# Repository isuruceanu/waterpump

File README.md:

# waterpump
water pump controller with digital pressure reader

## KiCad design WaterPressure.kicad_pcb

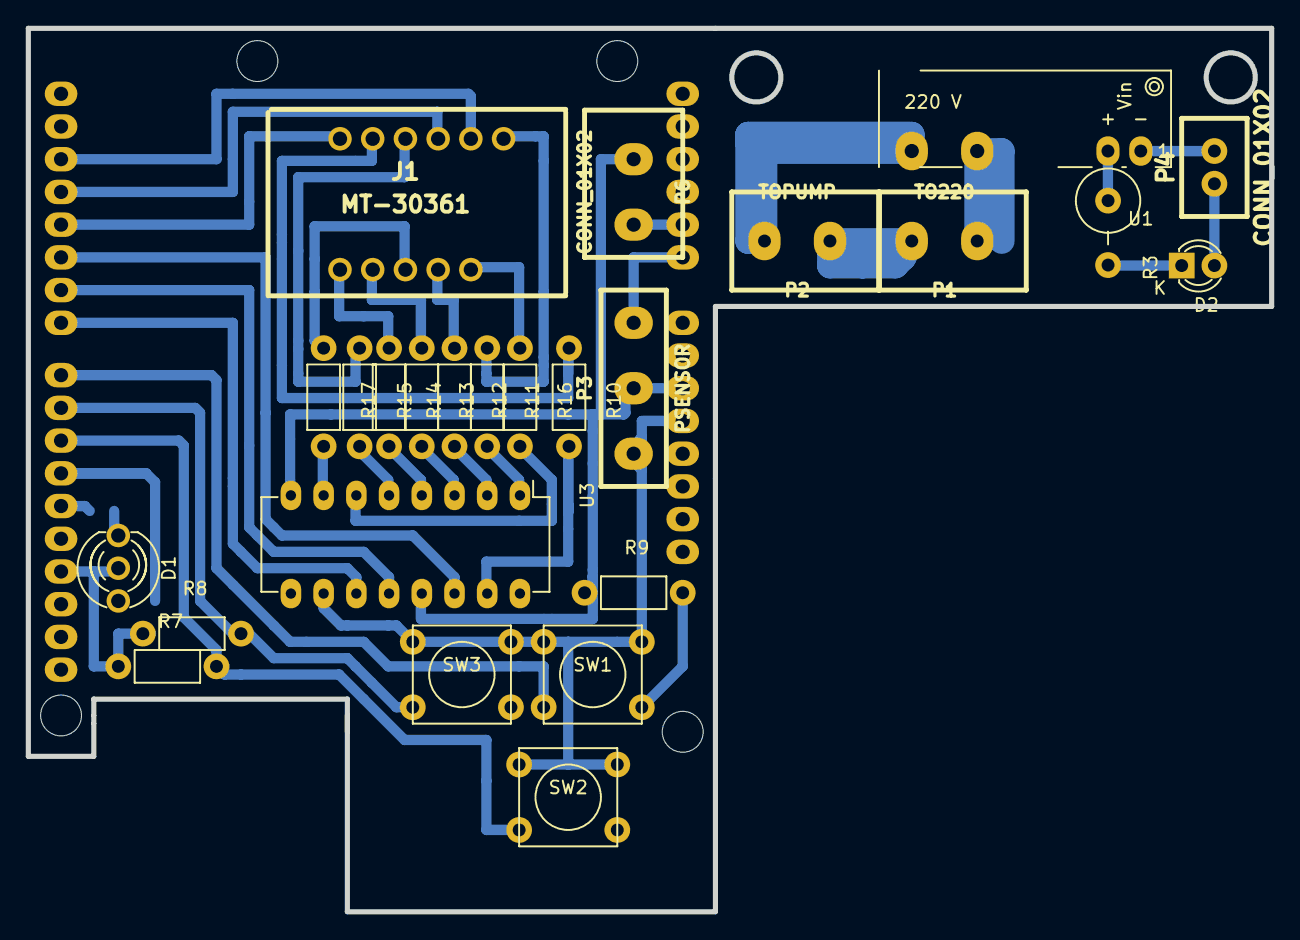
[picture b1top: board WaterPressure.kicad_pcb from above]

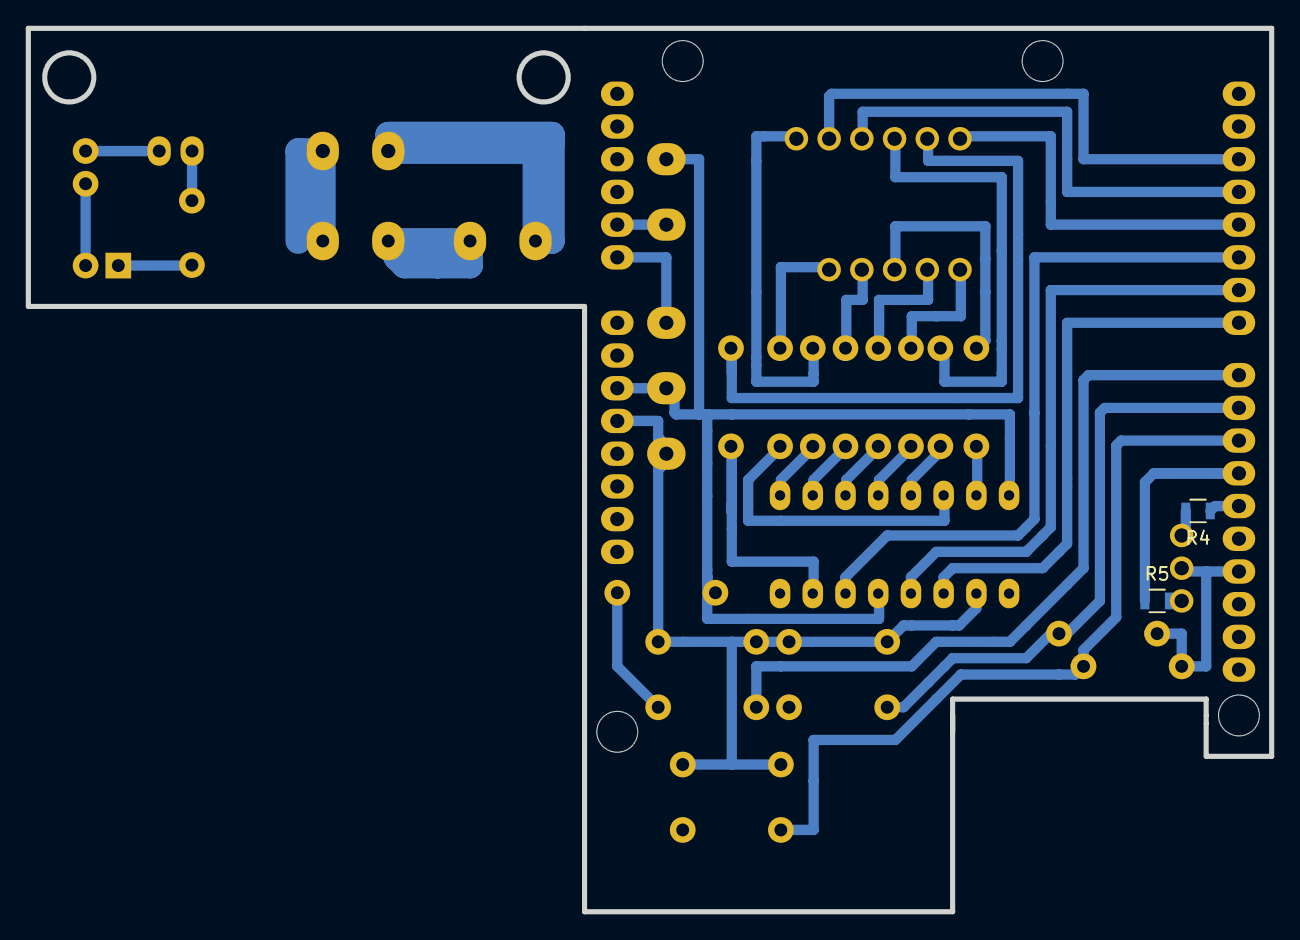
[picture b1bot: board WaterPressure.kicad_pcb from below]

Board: 2 copper layers, 96.5 x 68.6 mm, 28 parts (2 on the bottom side), 40 nets.

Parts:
D1: CLED; LED-5MM-3
D2: LED; LED-3MM
J1: MT-30361
P1: TO220; DG306-5.08-02
P2: TOPUMP; DG306-5.08-02
P3: PSENSOR; DG306-5.08-03
P4: CONN_01X02; DG306-2.54-02
P6: CONN_01X02; DG306-5.08-02
R3: 150; Resistor_Vertical_RM5mm
R4, R5: 330; R_0805
R7, R8, R9: 10k; Resistor_Horizontal_RM7mm
R10, R11, R12, R13, R14, R15, R16, R17: 220; Resistor_Horizontal_RM7mm
SHIELD1: ARDUINO_FOOTPRINT; ARDUINO_SHIELD
SW1, SW2, SW3: SW_PUSH; SW_PUSH_SMALL
U1: S102S01; DCDC-Conv_TRACO_TMH-xxxx_Single_RevB
U3: 74HC595; DIP-16_W7.62mm_LongPads

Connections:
+5V: P3.3, SHIELD1.5V, SW1.1, SW2.1, SW3.1, U3.10
BTN1: R7.2, SHIELD1.10, SW2.2
BTN2: R8.2, SHIELD1.9, SW3.2
BTN3: R9.2, SHIELD1.8, SW1.2
DISCLOCK: SHIELD1.7, U3.11
DISDATA: SHIELD1.5, U3.14
DISDIGI1: J1.12, SHIELD1.4
DISDIGI2: J1.9, SHIELD1.3
DISDIGI3: J1.8, SHIELD1.2
DISLATCH: SHIELD1.6, U3.12
GND: D1.2, P3.2, P6.2, R7.1, R8.1, R9.1, SHIELD1.GND1, SHIELD1.GND2, SHIELD1.GND3, U3.8, U3.13
LEDG: R5.1, SHIELD1.11
LEDR: R4.1, SHIELD1.12
unnamed: D1.1, R4.2
unnamed: D1.3, R5.2
unnamed: D2.1, R3.2
unnamed: D2.2, P4.2
unnamed: J1.1, R14.1
unnamed: J1.2, R13.1
unnamed: J1.3, R17.1
unnamed: J1.4, R12.1
unnamed: J1.5, R16.1
unnamed: J1.7, R11.1
unnamed: J1.10, R15.1
unnamed: J1.11, R10.1
unnamed: P1.1, P2.2
unnamed: P1.2, U1.1
unnamed: P2.1, U1.2
unnamed: P4.1, U1.4
unnamed: R3.1, U1.3
unnamed: R10.2, U3.15
unnamed: R11.2, U3.1
unnamed: R12.2, U3.2
unnamed: R13.2, U3.3
unnamed: R14.2, U3.4
unnamed: R15.2, U3.5
unnamed: R16.2, U3.6
unnamed: R17.2, U3.7
PINPUMP: P6.1, SHIELD1.AD1
PresureSensor: P3.1, SHIELD1.AD0

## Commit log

2016-08-08 added freetronic as subproject, added git ignore file
2016-08-08 changed arduino footprint
2016-08-09 drawing pcb , work in progress
2016-08-10 pcb finished
